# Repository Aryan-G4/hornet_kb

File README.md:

# hornet_kb
Hardware and Firmware for the Hornet Keyboard: a wireless. split. lowprofile hotswap keybaord

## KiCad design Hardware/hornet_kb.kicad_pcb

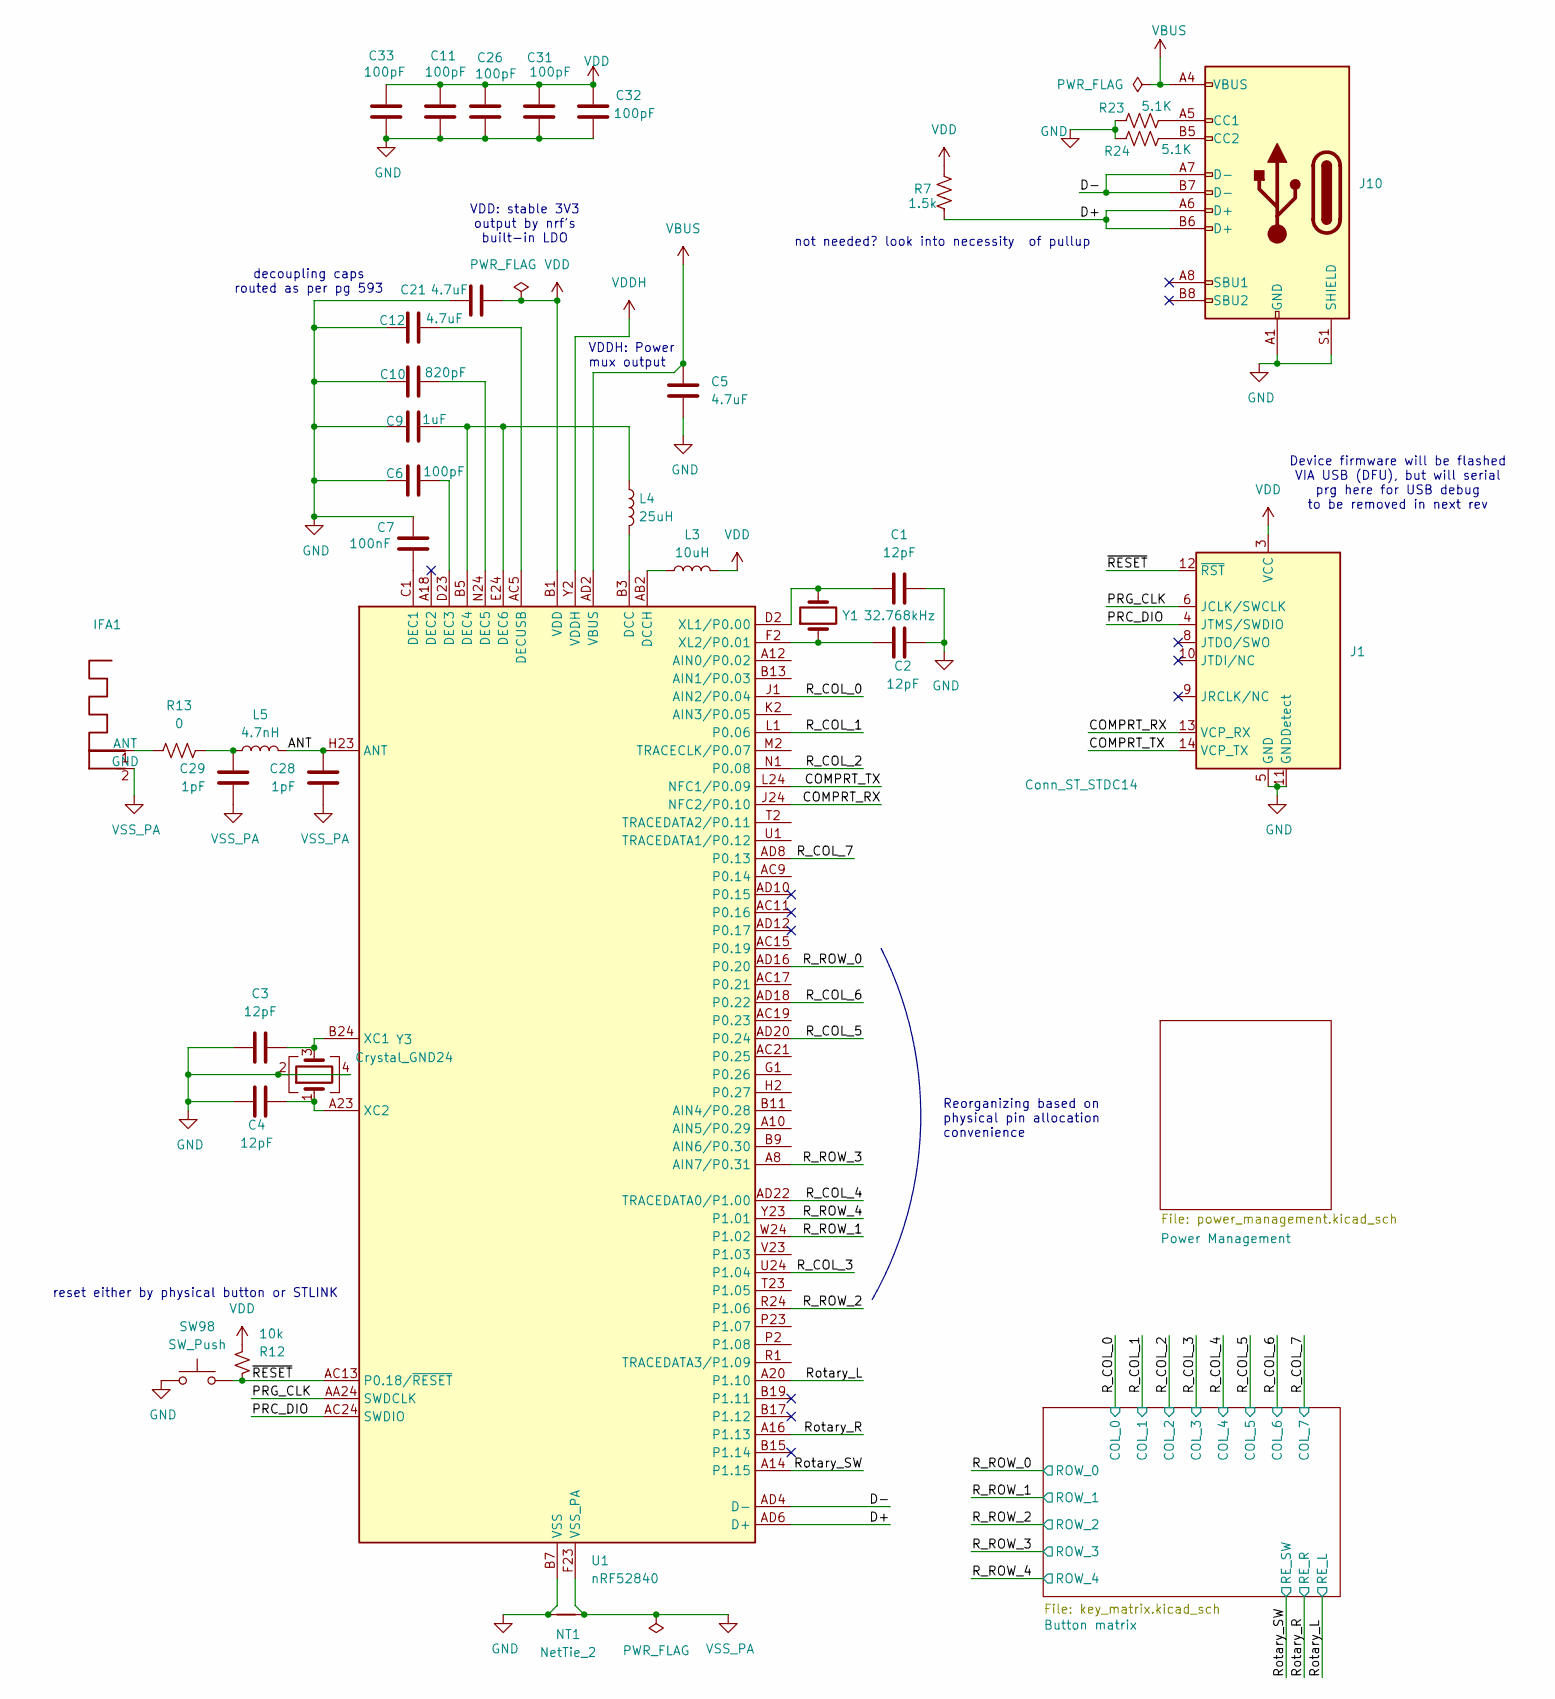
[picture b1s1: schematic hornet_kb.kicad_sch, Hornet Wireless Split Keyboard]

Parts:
C1, C2, C3, C4: 12pF; C_0402_1005Metric
C5, C12, C21: 4.7uF; C_0805_2012Metric
C6, C11, C26, C31, C32, C33: 100pF; C_0603_1608Metric
C7: 100nF; C_0603_1608Metric
C9: 1uF; C_0603_1608Metric
C10: 820pF; C_0603_1608Metric
C28, C29: 1pF; C_0402_1005Metric
IFA1: Texas_SWRA117D_2.4GHz_Right
J1: Conn_ST_STDC14; Tag-Connect_TC2070-IDC-FP_2x07_P1.27mm_Vertical
J10: USB_C_Receptacle_USB2.0; USB_C_Receptacle_HRO_TYPE-C-31-M-12; LCSC C165948
L3: 10uH; L_0402_1005Metric
L4: 25uH; L_0402_1005Metric
L5: 4.7nH; L_0402_1005Metric
NT1: NetTie_2; NetTie-2_SMD_Pad2.0mm
R7: 1.5k; R_0603_1608Metric; LCSC C23345
R12: 10k; R_0603_1608Metric
R13: 0; R_0402_1005Metric
R23, R24: 5.1K; R_0603_1608Metric; LCSC C23186
SW98: SW_Push; SW_Push_1P1T-MP_NO_Horizontal_Alps_SKRTLAE010
U1: nRF52840; Nordic_AQFN-73-1EP_7x7mm_P0.5mm
Y1: 32.768kHz; Crystal_SMD_3215-2Pin_3.2x1.5mm
Y3: Crystal_GND24; Crystal_SMD_2016-4Pin_2.0x1.6mm

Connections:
/ANT: C28.1, L5.1, U1.H23 (ANT)
/COMPRT_RX: J1.13 (VCP_RX), U1.J24 (NFC2/P0.10)
/COMPRT_TX: J1.14 (VCP_TX), U1.L24 (NFC1/P0.09)
/D+: J10.A6 (D+), J10.B6 (D+), R7.2, U1.AD6 (D+)
/D-: J10.A7 (D-), J10.B7 (D-), U1.AD4 (D-)
/PRC_DIO: J1.4 (JTMS/SWDIO), U1.AC24 (SWDIO)
/PRG_CLK: J1.6 (JCLK/SWCLK), U1.AA24 (SWDCLK)
/R_COL_0: U1.J1 (AIN2/P0.04); also elsewhere on the board
/R_COL_1: U1.L1 (P0.06); also elsewhere on the board
/R_COL_2: U1.N1 (P0.08); also elsewhere on the board
/R_COL_3: U1.U24 (P1.04); also elsewhere on the board
/R_COL_4: U1.AD22 (TRACEDATA0/P1.00); also elsewhere on the board
/R_COL_5: U1.AD20 (P0.24); also elsewhere on the board
/R_COL_6: U1.AD18 (P0.22); also elsewhere on the board
/R_COL_7: U1.AD8 (P0.13); also elsewhere on the board
/R_ROW_0: U1.AD16 (P0.20); also elsewhere on the board
/R_ROW_1: U1.W24 (P1.02); also elsewhere on the board
/R_ROW_2: U1.R24 (P1.06); also elsewhere on the board
/R_ROW_3: U1.A8 (AIN7/P0.31); also elsewhere on the board
/R_ROW_4: U1.Y23 (P1.01); also elsewhere on the board
/Rotary_L: U1.A20 (P1.10); also elsewhere on the board
/Rotary_R: U1.A16 (P1.13); also elsewhere on the board
/Rotary_SW: U1.A14 (P1.15); also elsewhere on the board
/~RESET: J1.12 (~RST), R12.2, SW98.1, U1.AC13 (P0.18/~RESET)
GND: C1.1, C2.1, C3.1, C4.1, C5.2, C6.2, C7.2, C9.2, C10.1, C11.2, C12.2, C21.1, C26.2, C31.2, C32.2, C33.2, J1.5 (GND), J1.7 (GND), J1.11 (GNDDetect), J10.A1 (GND), J10.A12 (GND), J10.B1 (GND), J10.B12 (GND), J10.S1 (SHIELD), NT1.2, R23.1, R24.1, SW98.2, U1.B7 (VSS), U1.EP (VSS), Y3.2, Y3.4; also elsewhere on the board
unnamed: C29.1, L5.2, R13.2
unnamed: IFA1.1 (ANT), R13.1
unnamed: J10.A5 (CC1), R23.2
unnamed: J10.B5 (CC2), R24.2
unnamed: L4.1, U1.B3 (DCC)
unnamed: L3.2, U1.AB2 (DCCH)
unnamed: C7.1, U1.C1 (DEC1)
unnamed: C6.1, U1.D23 (DEC3)
unnamed: C9.1, L4.2, U1.B5 (DEC4), U1.E24 (DEC6)
unnamed: C10.2, U1.N24 (DEC5)
unnamed: C12.1, U1.AC5 (DECUSB)
unnamed: C3.2, U1.B24 (XC1), Y3.3
unnamed: C4.2, U1.A23 (XC2), Y3.1
unnamed: C1.2, U1.D2 (XL1/P0.00), Y1.2
unnamed: C2.2, U1.F2 (XL2/P0.01), Y1.1
VBUS: C5.1, J10.A4 (VBUS), J10.A9 (VBUS), J10.B4 (VBUS), J10.B9 (VBUS), U1.AD2 (VBUS); also elsewhere on the board
VDD: C11.1, C21.2, C26.1, C31.1, C32.1, C33.1, J1.3 (VCC), L3.1, R7.1, R12.1, U1.A22 (VDD), U1.AD14 (VDD), U1.AD23 (VDD), U1.B1 (VDD), U1.W1 (VDD); also elsewhere on the board
VDDH: U1.Y2 (VDDH); also elsewhere on the board
VSS_PA: C28.2, C29.2, IFA1.2 (GND), NT1.1, U1.F23 (VSS_PA)

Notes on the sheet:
Reorganizing based on physical pin allocation convenience
VDDH: Power mux output
Device firmware will be flashed VIA USB (DFU), but will serial prg here for USB debug to be removed in next rev
decoupling caps routed as per pg 593
VDD: stable 3V3 output by nrf's built-in LDO
reset either by physical button or STLINK
not needed? look into necessity of pullup

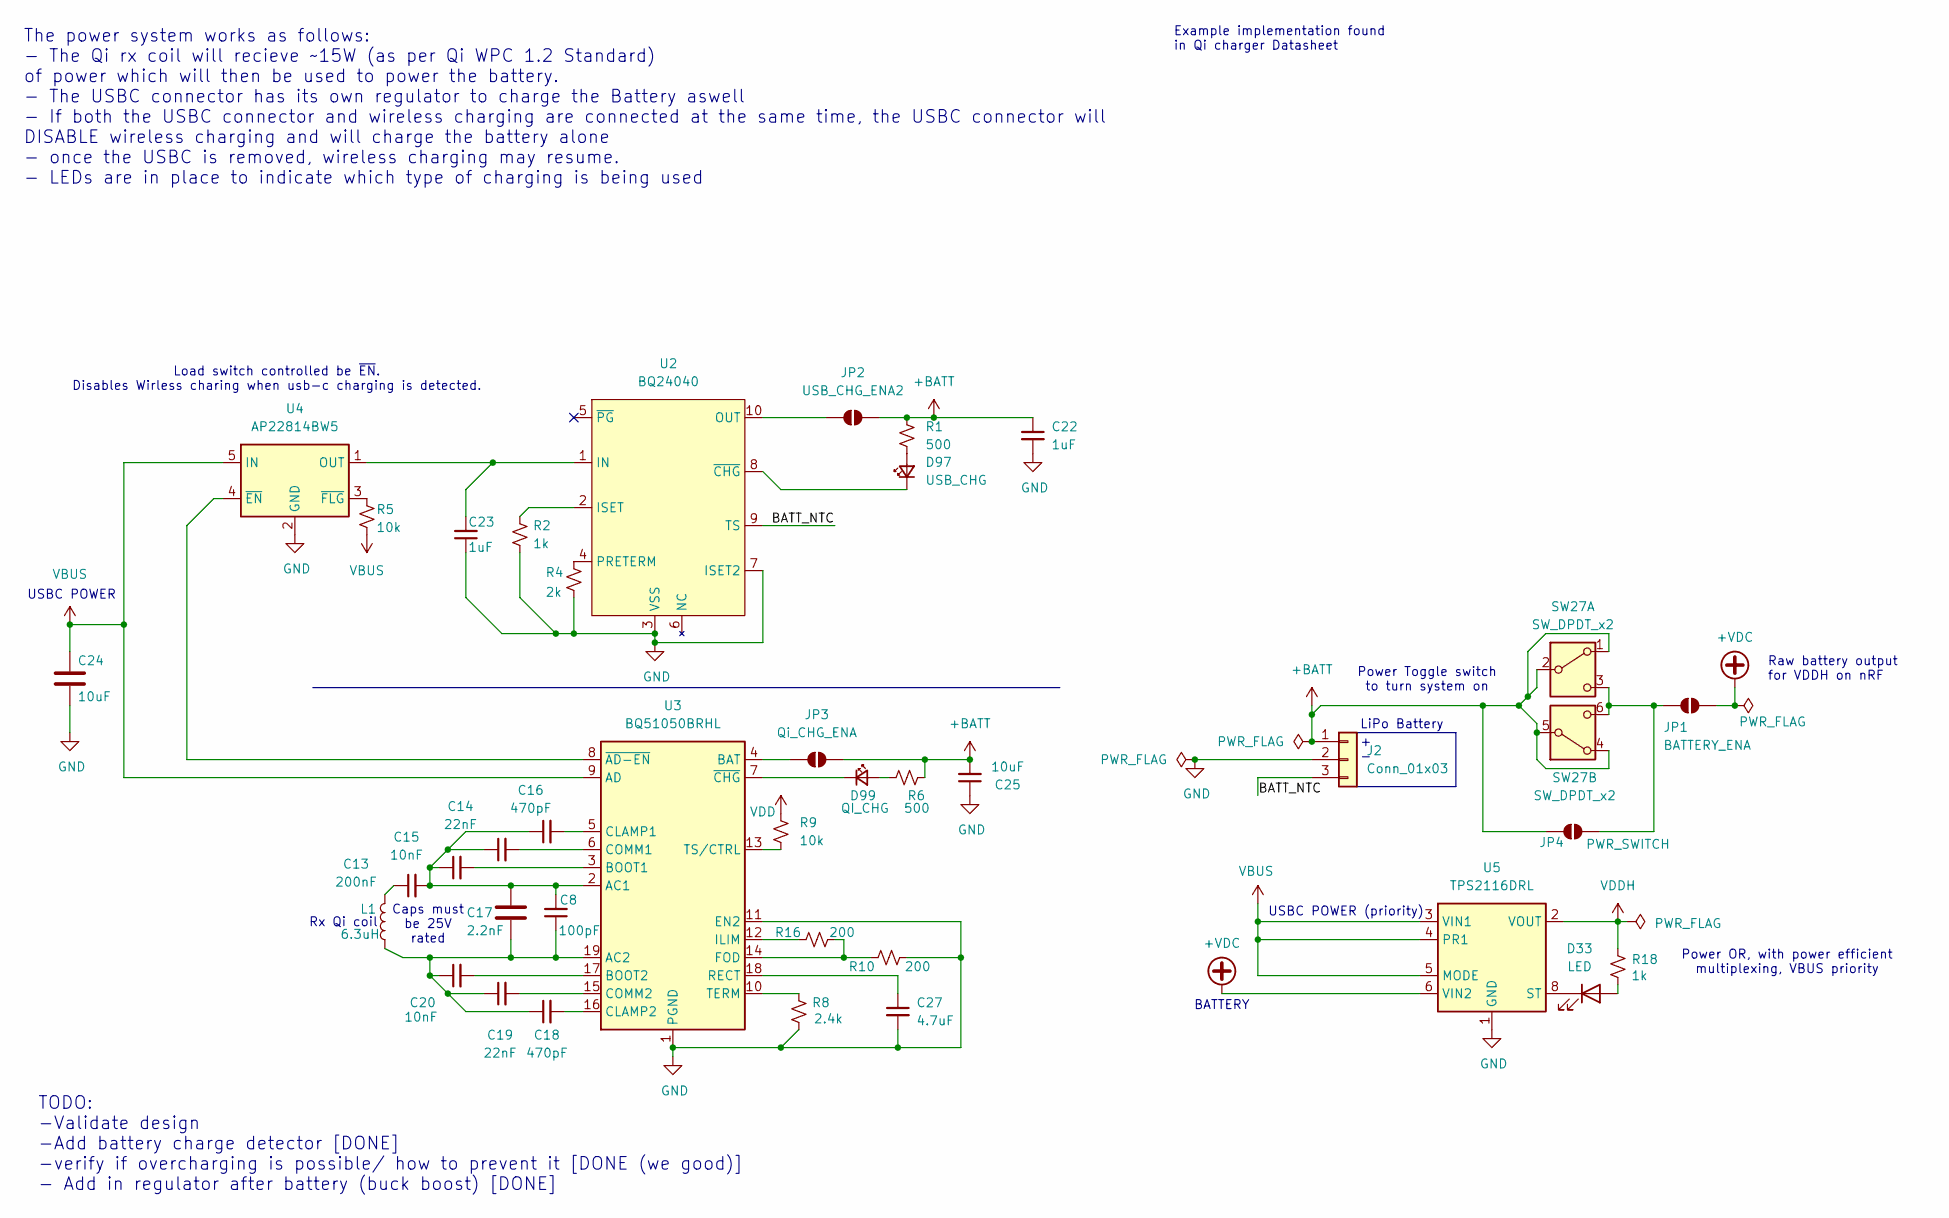
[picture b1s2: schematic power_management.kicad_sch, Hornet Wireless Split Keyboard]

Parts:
C8: 100pF; C_0603_1608Metric
C13: 200nF; C_0603_1608Metric
C14, C19: 22nF; C_0603_1608Metric
C15, C20: 10nF; C_0603_1608Metric
C16, C18: 470pF; C_0603_1608Metric
C17: 2.2nF; C_0603_1608Metric
C22, C23: 1uF; C_0603_1608Metric
C24, C25: 10uF; C_0603_1608Metric
C27: 4.7uF; C_0603_1608Metric
D33: LED; LED_0402_1005Metric
D97: USB_CHG; LED_0402_1005Metric
D99: QI_CHG; LED_0402_1005Metric
J2: Conn_01x03; JST_GH_SM03B-GHS-TB_1x03-1MP_P1.25mm_Horizontal
JP1: BATTERY_ENA; SolderJumper-2_P1.3mm_Open_TrianglePad1.0x1.5mm
JP2: USB_CHG_ENA2; SolderJumper-2_P1.3mm_Open_TrianglePad1.0x1.5mm
JP3: Qi_CHG_ENA; SolderJumper-2_P1.3mm_Open_TrianglePad1.0x1.5mm
JP4: PWR_SWITCH; SolderJumper-2_P1.3mm_Open_TrianglePad1.0x1.5mm
L1: 6.3uH; JST_EH_S2B-EH_1x02_P2.50mm_Horizontal
R1, R6: 500; R_0603_1608Metric
R2, R18: 1k; R_0603_1608Metric
R4: 2k; R_0603_1608Metric
R5, R9: 10k; R_0603_1608Metric
R8: 2.4k; R_0603_1608Metric
R10, R16: 200; R_0603_1608Metric
SW27: SW_DPDT_x2; SW_CK_JS202011CQN_DPDT_Straight
U2: BQ24040; Texas_DLH0010A_WSON-10-1EP_2.2x2mm_P0.4mm_EP0.9x1.5mm_Therm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
U3: BQ51050BRHL; Texas_VQFN-RHL-20
U4: AP22814BW5; SOT-23-5
U5: TPS2116DRL; SOT-583-8

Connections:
+BATT: C22.1, C25.2, J2.1, JP2.2 (B), JP3.2 (B), JP4.1 (A), R1.1, R6.1, SW27.1 (A), SW27.2 (B), SW27.4 (A), SW27.5 (B)
+VDC: JP1.2 (B), U5.6 (VIN2)
/Power Management/BATT_NTC: J2.3, U2.9 (TS)
GND: C22.2, C23.1, C24.2, C25.1, C27.2, J2.2, R2.1, R4.1, R8.2, R10.2, U2.3 (VSS), U2.7 (ISET2), U3.1 (PGND), U3.11 (EN2), U3.20 (PGND), U3.21 (PGND), U4.2 (GND), U5.1 (GND); also elsewhere on the board
unnamed: C13.1, L1.2
unnamed: D33.2 (A), R18.1
unnamed: D33.1 (K), U5.8 (ST)
unnamed: D97.2 (A), R1.2
unnamed: D97.1 (K), U2.8 (~CHG)
unnamed: D99.2 (A), R6.2
unnamed: D99.1 (K), U3.7 (~CHG)
unnamed: JP1.1 (A), JP4.2 (B), SW27.3 (C), SW27.6 (C)
unnamed: JP2.1 (A), U2.10 (OUT)
unnamed: JP3.1 (A), U3.4 (BAT)
unnamed: C23.2, U2.1 (IN), U4.1 (OUT)
unnamed: R2.2, U2.2 (ISET)
unnamed: R4.2, U2.4 (PRETERM)
unnamed: C8.2, C13.2, C14.1, C15.1, C16.1, C17.1, U3.2 (AC1)
unnamed: C8.1, C17.2, C18.1, C19.1, C20.1, L1.1, U3.19 (AC2)
unnamed: C15.2, U3.3 (BOOT1)
unnamed: C20.2, U3.17 (BOOT2)
unnamed: C16.2, U3.5 (CLAMP1)
unnamed: C18.2, U3.16 (CLAMP2)
unnamed: C14.2, U3.6 (COMM1)
unnamed: C19.2, U3.15 (COMM2)
unnamed: R10.1, R16.2, U3.14 (FOD)
unnamed: R16.1, U3.12 (ILIM)
unnamed: C27.1, U3.18 (RECT)
unnamed: R8.1, U3.10 (TERM)
unnamed: R9.2, U3.13 (TS/CTRL)
unnamed: U3.8 (~AD-EN), U4.4 (~EN)
unnamed: R5.2, U4.3 (~FLG)
VBUS: C24.1, R5.1, U3.9 (AD), U4.5 (IN), U5.3 (VIN1), U5.4 (PR1), U5.5 (MODE); also elsewhere on the board
VDD: R9.1; also elsewhere on the board
VDDH: R18.2, U5.2 (VOUT), U5.7 (VOUT); also elsewhere on the board

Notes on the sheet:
Power OR, with power efficient multiplexing, VBUS priority
Rx Qi coil
The power system works as follows: - The Qi rx coil will recieve ~15W (as per Qi WPC 1.2 Standard) of power which will then be used to power the battery. - The USBC connector has its own regulator to charge the Battery aswell - If both the USBC connector and wireless charging are connected at the s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
Raw battery output for VDDH on nRF
USBC POWER (priority)
USBC POWER
LiPo Battery
Example implementation found in Qi charger Datasheet
BATTERY
Caps must be 25V rated
Load switch controlled be ~{EN}. Disables Wirless charing when usb-c charging is detected.
Power Toggle switch to turn system on
+ -
TODO: -Validate design -Add battery charge detector [DONE] -verify if overcharging is possible/ how to prevent it [DONE (we good)] - Add in regulator after battery (buck boost) [DONE]

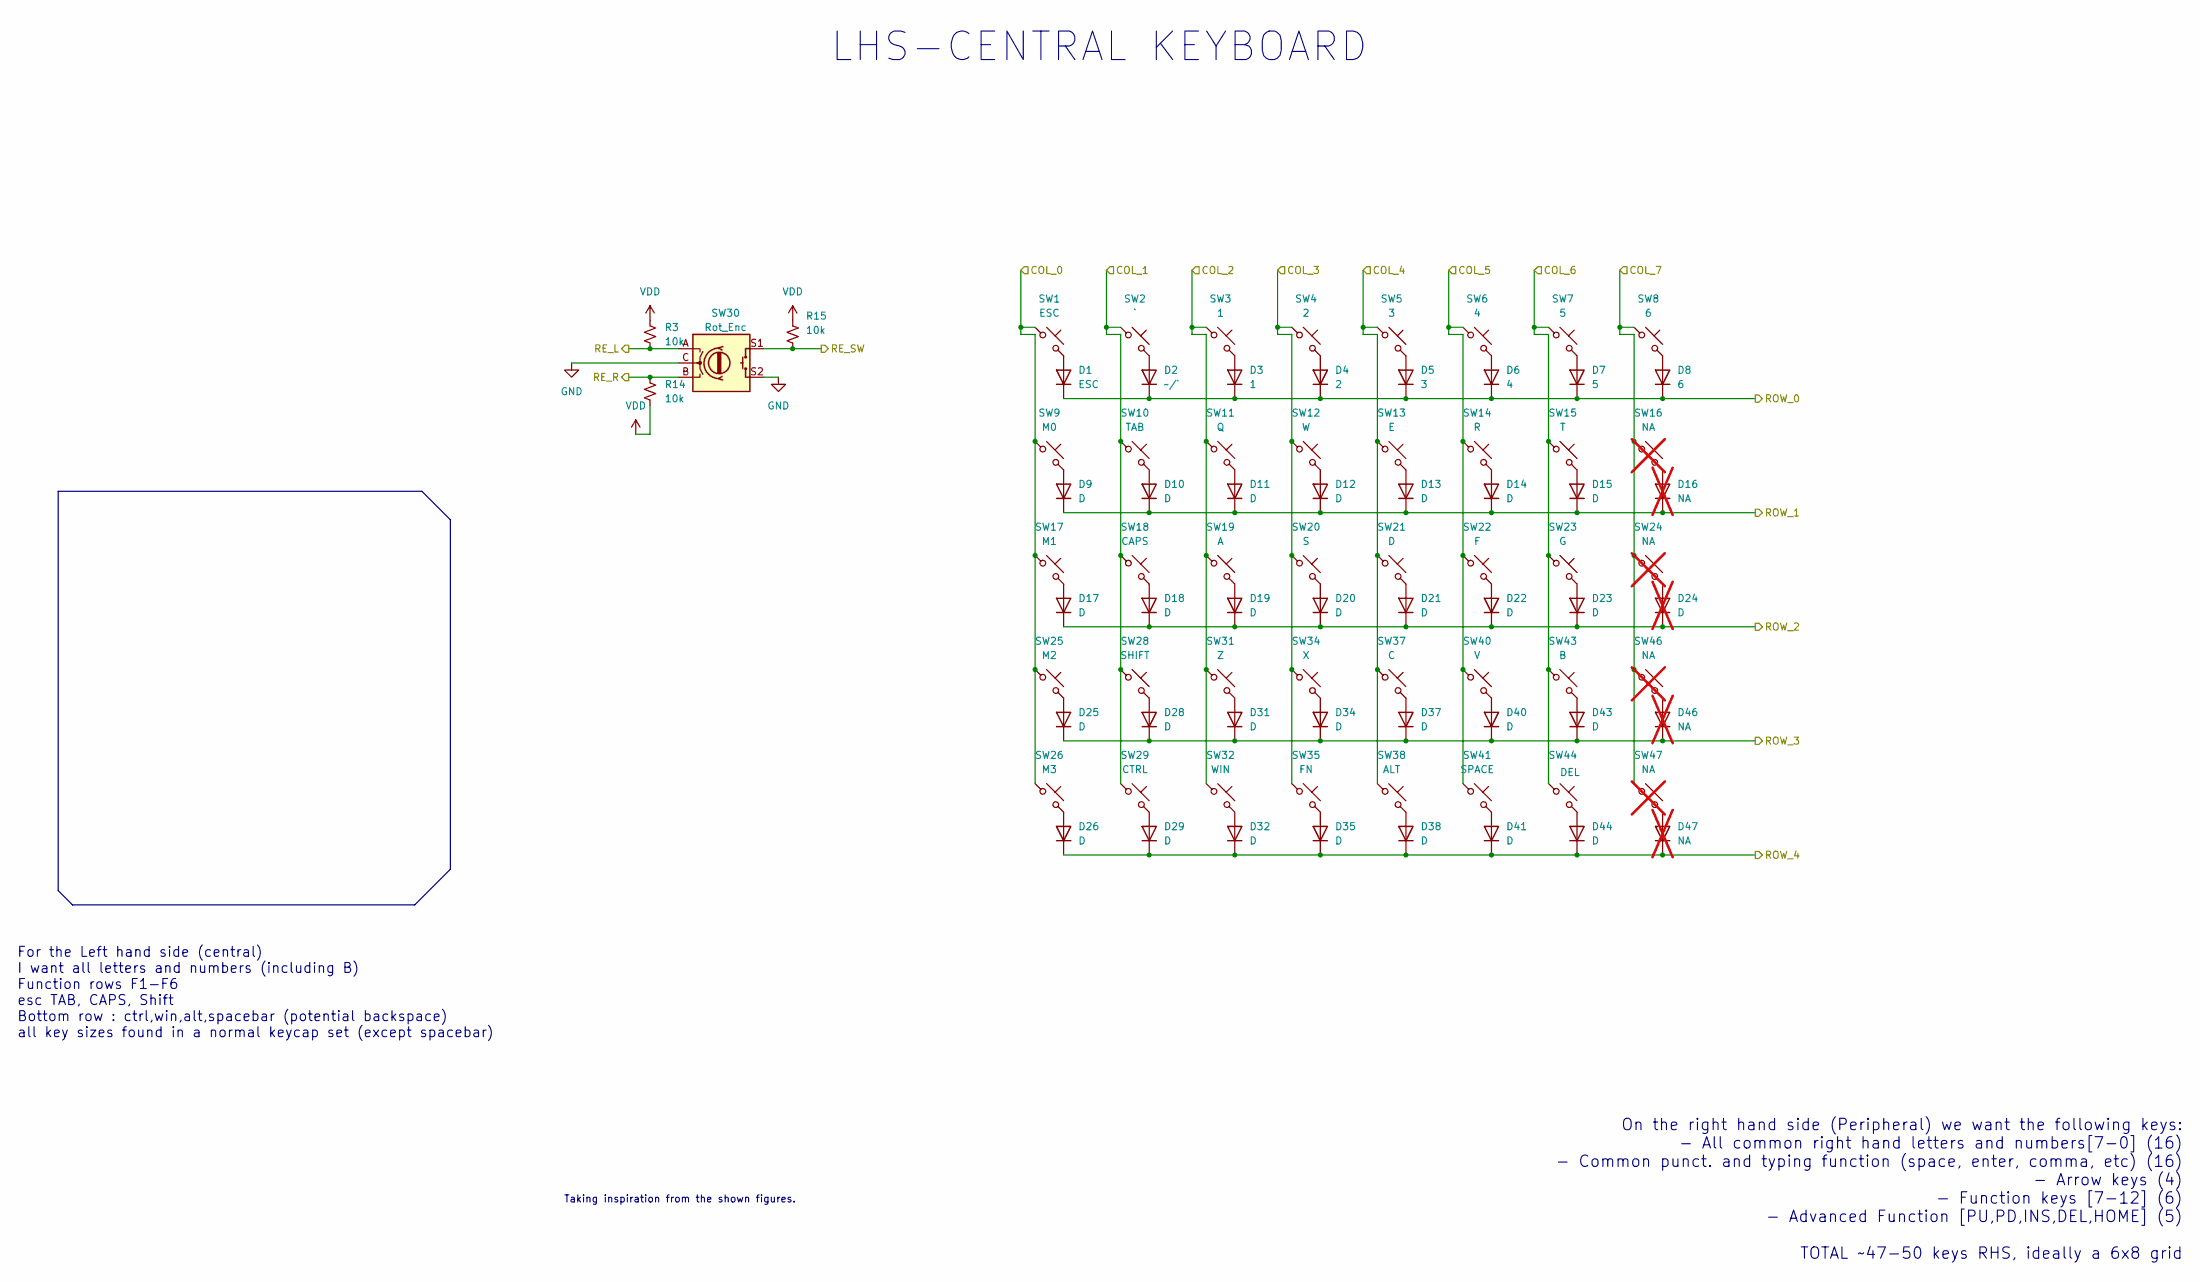
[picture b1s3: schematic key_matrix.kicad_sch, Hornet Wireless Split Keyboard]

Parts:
D1: ESC; Diode_SOD-123
D2: ~/`; Diode_SOD-123
D3: 1; Diode_SOD-123
D4: 2; Diode_SOD-123
D5: 3; Diode_SOD-123
D6: 4; Diode_SOD-123
D7: 5; Diode_SOD-123
D8: 6; Diode_SOD-123
D9, D10, D11, D12, D13, D14, D15, D17, D18, D19, D20, D21, D22, D23, D25, D26, D28, D29, D31, D32, D34, D35, D37, D38, D40, D41, D43, D44: D; Diode_SOD-123
D16, D46, D47: NA; Diode_SOD-123; not fitted
D24: D; Diode_SOD-123; not fitted
R3, R14, R15: 10k; R_0603_1608Metric
SW1: ESC; Hotswap_MX_1.00u
SW2: `; Hotswap_MX_1.00u
SW3: 1; Hotswap_MX_1.00u
SW4: 2; Hotswap_MX_1.00u
SW5: 3; Hotswap_MX_1.00u
SW6: 4; Hotswap_MX_1.00u
SW7: 5; Hotswap_MX_1.00u
SW8: 6; Hotswap_MX_1.00u
SW9: M0; Hotswap_MX_1.00u
SW10: TAB; Hotswap_MX_1.50u
SW11: Q; Hotswap_MX_1.00u
SW12: W; Hotswap_MX_1.00u
SW13: E; Hotswap_MX_1.00u
SW14: R; Hotswap_MX_1.00u
SW15: T; Hotswap_MX_1.00u
SW16: NA; Hotswap_MX_1.00u; not fitted
SW17: M1; Hotswap_MX_1.00u
SW18: CAPS; Hotswap_MX_1.75u
SW19: A; Hotswap_MX_1.00u
SW20: S; Hotswap_MX_1.00u
SW21: D; Hotswap_MX_1.00u
SW22: F; Hotswap_MX_1.00u
SW23: G; Hotswap_MX_1.00u
SW24: NA; Hotswap_MX_1.50u; not fitted
SW25: M2; Hotswap_MX_1.00u
SW26: M3; Hotswap_MX_1.00u
SW28: SHIFT; Hotswap_MX_2.25u
SW29: CTRL; Hotswap_MX_1.25u
SW30: Rot_Enc; RotaryEncoder_Alps_EC11E-Switch_Vertical_H20mm
SW31: Z; Hotswap_MX_1.00u
SW32: WIN; Hotswap_MX_1.00u
SW34: X; Hotswap_MX_1.00u
SW35: FN; Hotswap_MX_1.25u
SW37: C; Hotswap_MX_1.00u
SW38: ALT; Hotswap_MX_1.25u
SW40: V; Hotswap_MX_1.00u
SW41: SPACE; Hotswap_MX_2.25u
SW43: B; Hotswap_MX_1.00u
SW44: DEL; Hotswap_MX_1.00u
SW46, SW47: NA; not fitted

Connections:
/R_COL_0: SW1.1, SW9.1, SW17.1, SW25.1, SW26.1; also elsewhere on the board
/R_COL_1: SW2.1, SW10.1, SW18.1, SW28.1, SW29.1; also elsewhere on the board
/R_COL_2: SW3.1, SW11.1, SW19.1, SW31.1, SW32.1; also elsewhere on the board
/R_COL_3: SW4.1, SW12.1, SW20.1, SW34.1, SW35.1; also elsewhere on the board
/R_COL_4: SW5.1, SW13.1, SW21.1, SW37.1, SW38.1; also elsewhere on the board
/R_COL_5: SW6.1, SW14.1, SW22.1, SW40.1, SW41.1; also elsewhere on the board
/R_COL_6: SW7.1, SW15.1, SW23.1, SW43.1, SW44.1; also elsewhere on the board
/R_COL_7: SW8.1, SW16.1, SW24.1, SW46.1, SW47.1; also elsewhere on the board
/R_ROW_0: D1.1 (K), D2.1 (K), D3.1 (K), D4.1 (K), D5.1 (K), D6.1 (K), D7.1 (K), D8.1 (K); also elsewhere on the board
/R_ROW_1: D9.1 (K), D10.1 (K), D11.1 (K), D12.1 (K), D13.1 (K), D14.1 (K), D15.1 (K), D16.1 (K); also elsewhere on the board
/R_ROW_2: D17.1 (K), D18.1 (K), D19.1 (K), D20.1 (K), D21.1 (K), D22.1 (K), D23.1 (K), D24.1 (K); also elsewhere on the board
/R_ROW_3: D25.1 (K), D28.1 (K), D31.1 (K), D34.1 (K), D37.1 (K), D40.1 (K), D43.1 (K), D46.1 (K); also elsewhere on the board
/R_ROW_4: D26.1 (K), D29.1 (K), D32.1 (K), D35.1 (K), D38.1 (K), D41.1 (K), D44.1 (K), D47.1 (K); also elsewhere on the board
/Rotary_L: R3.1, SW30.A; also elsewhere on the board
/Rotary_R: R14.2, SW30.B; also elsewhere on the board
/Rotary_SW: R15.1, SW30.S1; also elsewhere on the board
GND: SW30.C, SW30.S2; also elsewhere on the board
unnamed: D1.2 (A), SW1.2
unnamed: D2.2 (A), SW2.2
unnamed: D3.2 (A), SW3.2
unnamed: D4.2 (A), SW4.2
unnamed: D5.2 (A), SW5.2
unnamed: D6.2 (A), SW6.2
unnamed: D7.2 (A), SW7.2
unnamed: D8.2 (A), SW8.2
unnamed: D9.2 (A), SW9.2
unnamed: D10.2 (A), SW10.2
unnamed: D11.2 (A), SW11.2
unnamed: D12.2 (A), SW12.2
unnamed: D13.2 (A), SW13.2
unnamed: D14.2 (A), SW14.2
unnamed: D15.2 (A), SW15.2
unnamed: D16.2 (A), SW16.2
unnamed: D17.2 (A), SW17.2
unnamed: D18.2 (A), SW18.2
unnamed: D19.2 (A), SW19.2
unnamed: D20.2 (A), SW20.2
unnamed: D21.2 (A), SW21.2
unnamed: D22.2 (A), SW22.2
unnamed: D23.2 (A), SW23.2
unnamed: D24.2 (A), SW24.2
unnamed: D25.2 (A), SW25.2
unnamed: D26.2 (A), SW26.2
unnamed: D28.2 (A), SW28.2
unnamed: D29.2 (A), SW29.2
unnamed: D31.2 (A), SW31.2
unnamed: D32.2 (A), SW32.2
unnamed: D34.2 (A), SW34.2
unnamed: D35.2 (A), SW35.2
unnamed: D37.2 (A), SW37.2
unnamed: D38.2 (A), SW38.2
unnamed: D40.2 (A), SW40.2
unnamed: D41.2 (A), SW41.2
unnamed: D43.2 (A), SW43.2
unnamed: D44.2 (A), SW44.2
unnamed: D46.2 (A), SW46.2
unnamed: D47.2 (A), SW47.2
VDD: R3.2, R14.1, R15.2; also elsewhere on the board

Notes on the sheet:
For the Left hand side (central) I want all letters and numbers (including B) Function rows F1-F6 esc TAB, CAPS, Shift Bottom row : ctrl,win,alt,spacebar (potential backspace) all key sizes found in a normal keycap set (except spacebar)
On the right hand side (Peripheral) we want the following keys: - All common right hand letters and numbers[7-0] (16) - Common punct. and typing function (space, enter, comma, etc) (16) - Arrow keys (4) - Function keys [7-12] (6) - Advanced Function [PU,PD,INS,DEL,HOME] (5) TOTAL ~47-50 keys RHS, i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
LHS-CENTRAL KEYBOARD
Taking inspiration from the shown figures.

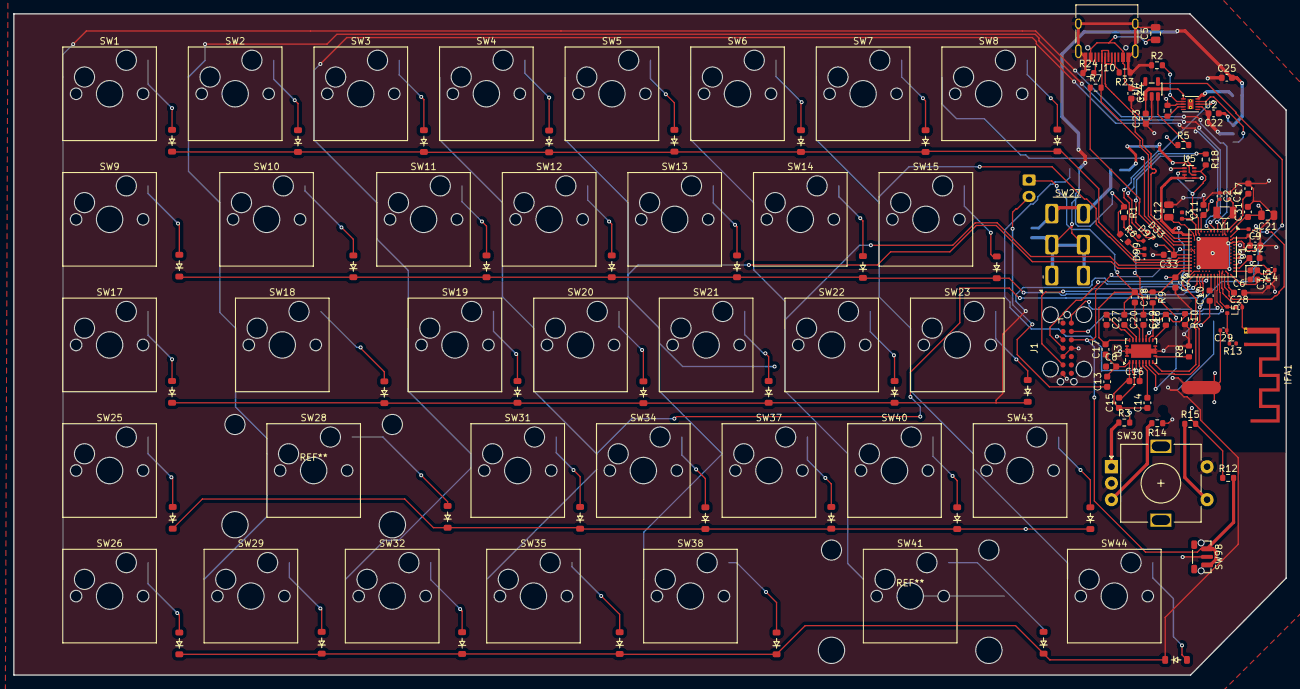
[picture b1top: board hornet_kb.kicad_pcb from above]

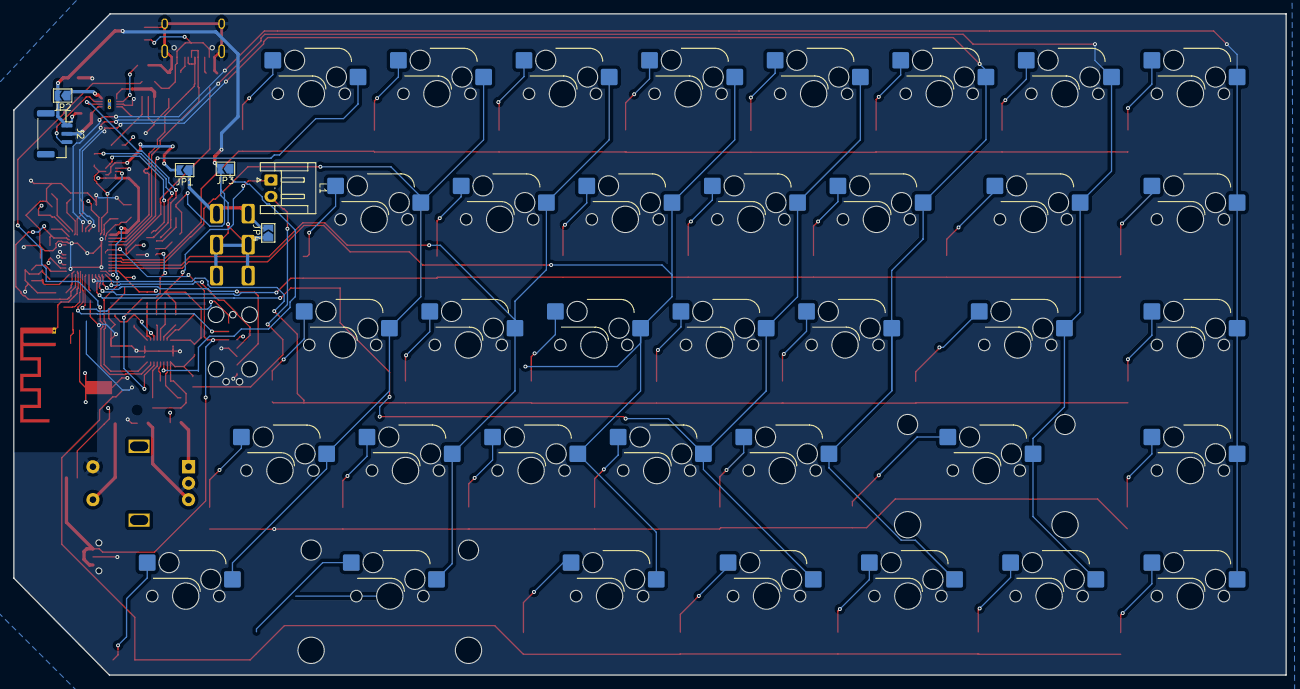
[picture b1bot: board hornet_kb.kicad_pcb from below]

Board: 4 copper layers, 193.0 x 100.3 mm, 148 parts (6 on the bottom side), 111 nets.

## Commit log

2025-09-19 Created Kicad project
2025-10-05 added new sheet for wireless comms
2025-10-05 init commit
2025-10-05 update gitignore
2025-10-05 Put in mcu and pwoer sheet
2025-10-05 update git ignore
2025-10-05 Added programmer and usbc
2025-10-08 remove autosaved files
2025-10-08 added in HS and LSref crystals
2025-10-09 Added external kicad library for niche ass footprints
2025-10-10 Complete draft of key matrix for both sides
2025-10-10 Added decoupling caps
2025-10-10 Draft and spec out power components
2025-10-11 Add design notes to key_matrix schematic
    Inserted a text block in key_matrix.kicad_sch detailing desired key layout and requirements for the left hand side of the keyboard.
2025-10-11 added sheet for wireless connectivity
2025-10-11 added sym for inverted f antenna
2025-10-11 added zander layout
2025-10-11 Moved BLE implementation into higherarchical page
2025-10-11 wired USB battery charger
2025-10-12 added footprint for IFA
2025-10-12 finish draft of power schematic
2025-10-12 updated gitignore
2025-10-14 Complete first ROUGH draft of schematic
2025-10-15 Added new keyboard layouts
2025-10-16 add datasheet to usb charger and fix erc
2025-10-16 renamed layout to left hand central
2025-10-17 Added rev4 of keyboard layout and organized all prev versions into a respective directory
2025-10-17 Named all LHS keys
2025-10-17 Completed Final GUI Key Layout and PCB key layout draft
2025-10-17 added stabilizers to layout
2025-10-17 Marked stabilizers as not in sch
2025-10-17 fix "T" key footprint
2025-10-18 Update footprints and switch symbol in schematic
    Set proper SMD footprints for capacitors, resistors, inductors, crystals, and net ties in hornet_kb.kicad_sch. In power_management.kicad_sch, replace DIP switch symbol with DPDT switch, update relate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
2025-10-18 Completed keymatrix layout
2025-10-19 Added LDO to battery and added placement for the charging modules
2025-10-19 Change labels from global to netlist
2025-10-19 Refactor keyboard and power schematics, remove backups
    Deleted old hornet_kb schematic backup ZIPs. Updated hornet_kb.kicad_sch: reorganized right-hand row/column labels and wires for physical pin convenience, added annotation, and removed redundant glob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
2025-10-19 Update schematic coordinates and add notes
    Adjusted coordinates for wires, junctions, and no_connects in hornet_kb.kicad_sch for improved layout clarity. Added company info and new design notes. Deleted outdated backup ZIP file.
2025-10-19 Add higherarchical pins to key matrix
2025-10-19 added rotary encoder to schematic
2025-10-19 added rotary enc higherarchical pins to mcu
2025-10-19 Update schematic for rotary encoder and matrix layout
    Added new symbols and labels for rotary encoder connections, updated wire routing and junctions, and adjusted matrix row/column positions for improved clarity and alignment. Also corrected text annot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
2025-10-19 Add antenna symbol and update schematic connections
    Introduced a new Device:Antenna symbol to the hornet_kb schematic and added its instance. Updated various wire and junction connections, including changes to VBUS, GND, and capacitor placements. Repl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
2025-10-19 Removed LDO (already one built into nrf)
2025-10-19 Update schematic for hornet_kb with new coordinates
    Adjusted coordinates for arcs, text, junctions, no_connects, and wires in hornet_kb.kicad_sch to reflect a new layout or grid. This includes moving various elements to new positions, removing and add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
2025-10-19 Update schematic files and add image to hornet_kb
    Adjusted text position in hornet_kb.kicad_sch, added a large embedded image, and updated key_matrix and power_management schematic files. These changes may improve documentation and visual references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
2025-10-20 Update power management wiring and resistor positions
    Added a PWR_FLAG symbol to hornet_kb schematic. Modified power_management schematic wiring, removed and added junctions, and adjusted wire connections for improved power routing. Relocated resistors 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
2025-10-20 Re-enable backup files
2025-10-20 Update PCB net names
2025-10-20 Changed C22 cap value
2025-10-20 assign footprints (rough draft)
2025-10-22 Route dual sided hotswap/diodes assmebly
2025-10-22 added extra decoupling caps to the mcu VDD pins
2025-10-22 changed pin allocations for keys based on physical location
2025-10-22 move MCU to prioritize BLE routing
2025-10-23 added in pwoer mux
2025-10-23 modified layout placement
2025-10-24 Fix ERC and stylistic errors
2025-10-24 Add Antenna Library to repo
2025-10-24 Finished draft placement of parts
2025-10-24 Update footprints and positions for multiple components
    Changed footprints, positions, and orientations for several components including LEDs, capacitors, net ties, ICs, and antenna in hornet_kb.kicad_pcb. These updates improve layout accuracy and reflect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
2025-10-24 Completed mcu routing
2025-10-25 Added jumper to override power switch
2025-10-25 FINISHED FIRST DRAFT OF LAYOUT!!
